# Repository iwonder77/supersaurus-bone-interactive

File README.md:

# Supersaurus Bone Interactive

Three-channel 555 monostable timer board driving RGB LED strips for a guess-the-dinosaur-bone exhibit at Thanksgiving Point's Museum of Ancient Life.

https://github.com/user-attachments/assets/5193e17a-1725-41bf-98e3-4b2cfe211b8b

---

## At a Glance

|                        |                                                               |
| ---------------------- | ------------------------------------------------------------- |
| **Supply**             | 12 V DC, single rail                                          |
| **Channels**           | 3 (one per answer slot)                                       |
| **Input per channel**  | Littlefuse reed switch (slot occupancy) AND master pushbutton |
| **Output pulse width** | `~3.63s` - set by R`33k` / C`100uF`                           |
| **Load per channel**   | 12V RGB LED strip, 1.67 A measured                            |
| **Load switching**     | Off-board N-channel MOSFET module, low-side                   |
| **PCB**                | `2-layer, 1 oz copper, HASL, 1.6 mm`                          |
| **Assembly**           | `JLCPCB Assembly and hand soldered`                           |
| **Active logic**       | Trigger is active-LOW; LED output is active-HIGH              |

---

## Overview

The Supersaurus bone interactive at Thanksgiving Point's Museum of Ancient Life invites visitors to guess which dinosaur the Supersaurus is related to based solely on scapula bone graphics. Guests place the Supersaurus scapula into one of three slots, each corresponding to a different dinosaur with its own scapula graphic. When they're ready to check their answer, they press a button, and an LED light strip installed behind the frosted acrylic slots briefly lights up red or green, providing immediate feedback on their guess.

When presented with the requirements of this project, my mind immediately jumped to using basic GPIO pins on a microcontroller to read the inputs, debounce them in software, and trigger a switching module for the lights. Even though that may have worked, removing software entirely for a three-input interaction with fixed timing removes an entire set of failure modes. A discrete analog implementation has no boot time, no watchdog to tune, and no flash to corrupt on abrupt power loss.

## Hardware Design Requirements

The interactive needed a circuit that:

- Debounces reed switch + button inputs for a smooth user experience
- Triggers immediate feedback on their answer for a short duration
- Resets the system quickly to not spoil the answer for the next guest
- Draws minimal power to handle reliable long term operation (next to 0 maintenance on parts)

These requirements quickly led to using a 555 timer in monostable mode to handle the timing portion of the interactive, and a MOSFET circuit to handle the fast and power efficient switching of a higher current load (LED strips).

## Main Hardware Components

- T.I. NE555P Timer ([datasheet](https://www.ti.com/lit/ds/symlink/ne555.pdf?ts=1777883502652))
- IRF520 MOSFET ([datasheet](https://www.vishay.com/docs/91017/irf520.pdf))
- PWM RGB LED Strips [link](https://www.amazon.com/dp/B0FSWXXXD4?ref=fed_asin_title&th=1)

The full BOM is included in the `manufacturing/` folder

## Full Schematic

## Main Hardware Architecture

Each 555 timer's TRIG pin is connected to a single reed switch (mounted behind the slot guests put the bone in), and each reed switch feeds into one "master" N.O. button. RC/pull up networks are configured for each TRIG pin to ensure smooth and predictable switching. This configuration allows the TRIG pin on each 555 timer to be pulled LOW only when its corresponding reed switch is closed **and** the button is pressed.

The three 555 timers are used in monostable mode to output a short pulse signal on pin Q when the TRIG pin is pulled low. More on monostable mode and the duration of the pulse below. The output signal (~10.3V when VCC = 12V) is fed into the gate of a IRF520 N-channel MOSFET module, which switches the low side of an RGB LED Strip for as long as the gate is driven.

## 555 Timer Notes

### Monostable Mode

Shorting the DISCHARGE and THRESHOLD pins of the 555 timer and routing them to an RC circuit operates the 555 timer in monostable mode. Ben Eater has a really great and informative series on the different 555 timer modes, I highly recommend watching them. Here's the one about [monostable mode](https://www.youtube.com/watch?v=81BgFhm2vz8).

In any case, the formula for the output signal duration is

$$
t_w = 1.1 \times R_A \times C
$$

Where $R_A$ and $C$ are the values of the resistor and capacitor. For future boards I wanted to make this duration configurable by having three open jumpers routed to resistors of different values (22k, 33k, 47k). The output pulse duration would change depending on which jumper is soldered.

Note: the trigger pulse must be shorter than $t_w$ and below $\frac{1}{3}V_{CC}$ (the 555's internal comparator threshold). If TRIG remains below $\frac{1}{3}V_{CC}$ beyond $t_w$, the output holds HIGH until TRIG rises.

### Power-on Reset Circuit

The 0.22uF and 10k RC network on the 555's RESET pin form a POR (power-on reset) circuit. During initial power-up testing without it, the output (Q) pin produced occasional HIGH pulses due to undefined internal states of the IC, which turned on downstream LED strips. This RC network briefly holds RESET low during power-up, forcing Q in a known LOW state while internal circuitry stabilizes. As the 0.22uF capacitor charges, RESET rises to VCC and normal operation begins, preventing false triggering at startup.

### Output (Q) Voltage

When triggered, the output voltage on pin Q isn't necessarily equal to VCC. When powered by 5V, I measured outputs of ~3.3V. When powered by 12V, I measured outputs of ~10.3V. The datasheet confirms this slight drop in voltage, and it is important to know since we'll be using it to drive the gate of an N-Channel MOSFET.

## MOSFET Selection and Gate Drive Design Notes

### Role

The main design requirements that guided my MOSFET selection were the following

- Fast switch times of 12V RGB LED strip loads (on the order of 1-2A)
- Minimal power dissipation
- Predictable operating behavior

Although quite outdated, the IRF520 N-Channel MOSFET was initially selected due to its accessibility, very low cost, and basic matching of electrical characteristics to the requirements described above (more on these below).

### Initial Implementation and Failure Mode

My initial prototype powered the 555 timer at VCC = 5V and used the output (Q) pin to directly drive the gate of an IRF520 MOSFET module. While the timing circuit functioned correctly, the LED strip failed to illuminate properly. This failure mode was not due to wiring or logic errors, but rather improper gate drive conditions for the selected MOSFET.

I'll start off by describing the important electrical characteristics we should know about for this design (for a deeper dive, refer to the [datasheet](https://www.vishay.com/docs/91017/irf520.pdf)). Then I'll discuss the proper gate drive design.

### Key Electrical Considerations

#### 1. $V_{GS(th)}$ Gate-Source Threshold Voltage

$V_{GS(th)} = 2.0\,\text{V}$ to $4.0\,\text{V}$ at $I_D = 250\,\mu\text{A}$

This parameter defines the voltage at which the MOSFET just barely begins to conduct a very small current - it is **not** an operating point for driving the gate and turning on the MOSFET. The best design drives the gate well past this threshold simply due to the fact that at higher gate voltages, the resistance between the drain-source ($R_{DS(on)}$) is much lower, leading to more efficient power operation.

#### 2. $R_{DS(on)}$ Drain-Source "on" Resistance

$R_{DS(on)} = 0.27\,\Omega$ at $V_{GS} = 10\,\text{V}$

For switching applications, the MOSFET must operate in the **ohmic (linear) region** (the $I_D$ vs. $V_{DS}$ graph below shows this region for various $V_{GS}$ curves) with as low a $R_{DS(on)}$ as possible. The lower the resistance, the less power is dissipated. To reach this lower resistance, we must drive the gate further and further from the threshold voltage (but don't exceed its maximum).

#### 3. $I_D$ vs. $V_{DS}$ graph at T = 25C (from datasheet)

<div align="center">
    <image src="docs/assets/ID-vs-VDS-curve.png" alt="id-vs-vds-curve">
</div>

In the ohmic region (linear region of the curves) the MOSFET acts like a voltage controlled resistor, where

$$
I_D = \frac{V_{DS}}{R_{DS(on)}}
$$

note that $R_{DS(on)}$ is not a fixed quantity, but decreases as $V_{GS}$ rises above $V_{GS(th)}$. The datasheet value of $0.27\,\Omega$ only holds at $V_{GS} = 10V$. Near the threshold voltage, it can be orders of magnitude higher, which directly increases power drawn ($P = I^2 * R$). Otherwise, in the saturation region, the MOSFET essentially acts as a current source, due to how the drain current $I_D$ stays nearly constant regardless of $V_{DS}$.

### Gate Drive Design

With the 555 timer powered at 5V, the output pin's HIGH voltage falls between 2.75V-3.3V (datasheet values). This is exactly in the MOSFET's $V_{GS(th)}$ range, where it barely starts to open and conduct current. Suppose our timer drove the gate at 3.3V, this would be a huge reliability concern, because:

- If the specific MOSFET we used had a $V_{GS(th)}$ = 2V: the MOSFET would slightly conduct
- If the MOSFET had a $V_{GS(th)}$ = 3.3V: the MOSFET would be right at threshold — essentially off
- If the MOSFET had a $V_{GS(th)}$ = 4V: the MOSFET wouldn't conduct at all

This doesn't even consider the inefficient power operation of the MOSFET in these conditions due to the very high $R_{DS(on)}$ and the 12V LED strip load demand. To ensure proper MOSFET operation, the gate drive voltage must be increased to a level where $R_{DS(on)}$ is low and well-defined.

Two viable approaches were considered:

#### Option 1: Use a Logic-Level MOSFET (IRLZ44N) with 5V supply for 555 timers

- Pros: compatible with lower level logic
- Cons: complicates power architecture (12V for LED strips and 5V for 555 timers)

#### Option 2: Increase Gate Drive Voltage (Selected)

Power the 555 timers at 12V (note: 5V sits at the lower bound of the NE555's recommended operating range, we should have started prototyping here). This results in:

- A gate drive voltage of ~10.3V
- A fully enhanced ("on") IRF520 with much lower $R_{DS(on)}$ and more manageable power dissipation
- A single 12V supply for the entire system

### Final Operating Behavior Calculations

Each LED strip draws 1.67A at 12V, measured directly on the bench. With the 555 timers powered at VCC = 12V, the gate sees ~10.3V - close to the datasheet condition of $V_{GS} = 10\text{V}$, so $R_{DS(on)} = 0.27\Omega$ applies directly.

The voltage drop across the MOSFET when fully on is

$$
V_{DS} = I_D \times R_{DS(on)} = 1.67\text{A} \times 0.27\Omega \approx 0.45\text{V}
$$

This confirms the MOSFET is in the ohmic region: ohmic operation requires $V_{DS} < V_{GS} - V_{GS(th)}$, and $0.45\text{V} \ll 10\text{V} - 2\text{V} = 8\text{V}$. The power dissipated by the MOSFET is then:

$$
P = I_D^2 \times R_{DS(on)} = (1.67\text{A})^2 \times 0.27\Omega \approx 0.75\text{W}
$$

At 0.75W, the IRF520 in its TO-220 package dissipates comfortably without a heatsink - a viable operating point for this application.

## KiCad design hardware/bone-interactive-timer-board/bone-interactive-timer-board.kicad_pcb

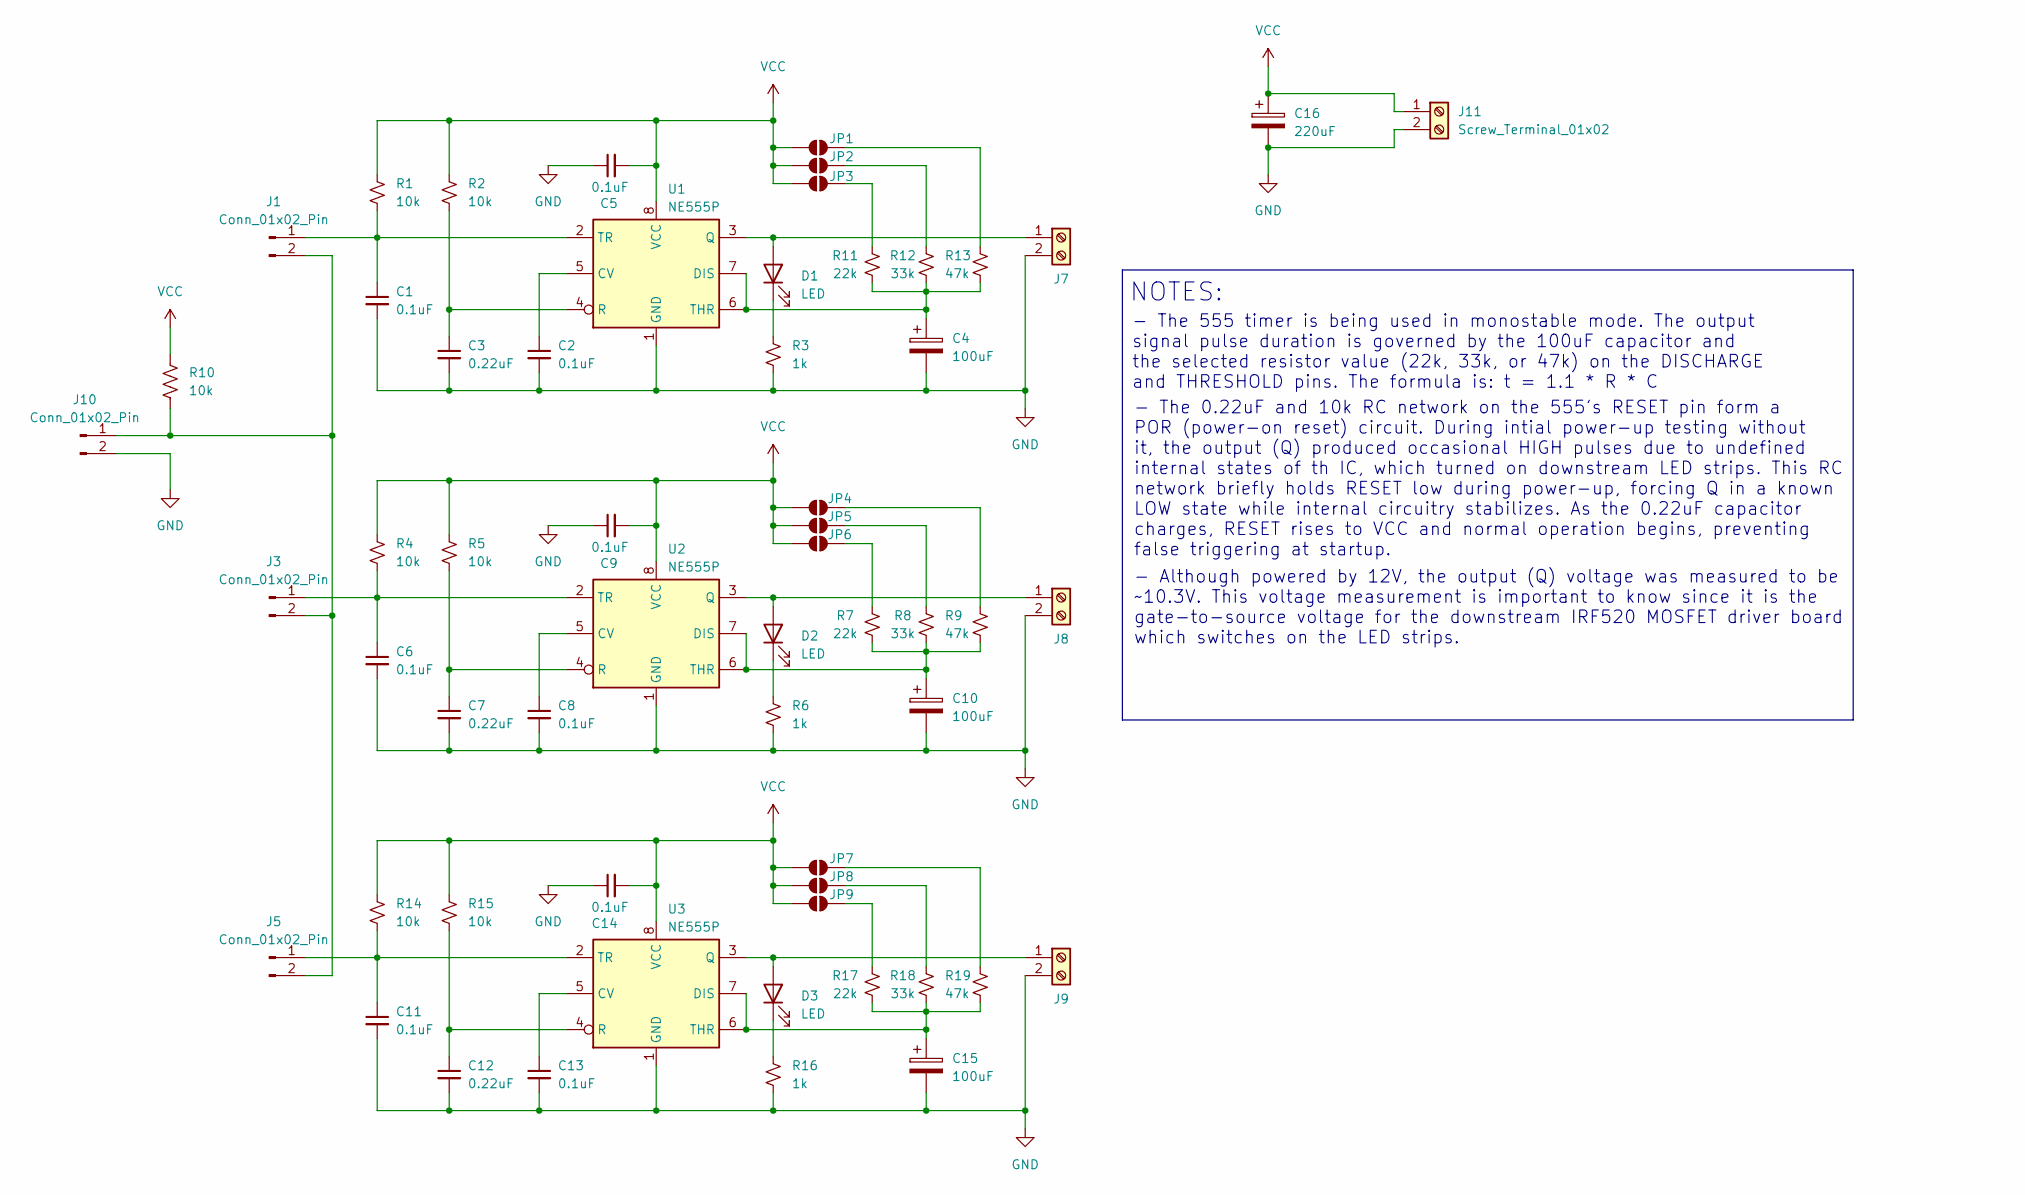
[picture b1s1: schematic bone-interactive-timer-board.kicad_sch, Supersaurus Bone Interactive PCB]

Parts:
C1, C2, C5, C6, C8, C9, C11, C13, C14: 0.1uF; C_0603_1608Metric
C3, C7, C12: 0.22uF; C_0603_1608Metric
C4, C10, C15: 100uF; CP_Elec_6.3x5.4
C16: 220uF; CP_Radial_D7.5mm_P2.50mm
D1, D2, D3: LED; LED_1206_3216Metric
J1, J3, J5, J10: Conn_01x02_Pin; PinHeader_1x02_P2.54mm_Vertical
J7, J8, J9, J11: Screw_Terminal_01x02; TerminalBlock_Phoenix_MPT-0,5-2-2.54_1x02_P2.54mm_Horizontal
JP1, JP2, JP3, JP4, JP5, JP6, JP7, JP8, JP9: SolderJumper_2_Open; SolderJumper-2_P1.3mm_Open_RoundedPad1.0x1.5mm
R1, R2, R4, R5, R10, R14, R15: 10k; R_0603_1608Metric
R3, R6, R16: 1k; R_0805_2012Metric
R7, R11, R17: 22k; R_0603_1608Metric
R8, R12, R18: 33k; R_0603_1608Metric
R9, R13, R19: 47k; R_0603_1608Metric
U1, U2, U3: NE555P; DIP-8_W7.62mm

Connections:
GND: C1.2, C2.2, C3.2, C4.2, C5.1, C6.2, C7.2, C8.2, C9.1, C10.2, C11.2, C12.2, C13.2, C14.1, C15.2, C16.2, J7.2, J8.2, J9.2, J10.2, J11.2, R3.1, R6.1, R16.1, U1.1 (GND), U2.1 (GND), U3.1 (GND)
unnamed: D1.2 (A), J7.1, U1.3 (Q)
unnamed: D1.1 (K), R3.2
unnamed: D2.2 (A), J8.1, U2.3 (Q)
unnamed: D2.1 (K), R6.2
unnamed: D3.2 (A), J9.1, U3.3 (Q)
unnamed: D3.1 (K), R16.2
unnamed: C1.1, J1.1, R1.2, U1.2 (TR)
unnamed: J1.2, J3.2, J5.2, J10.1, R10.2
unnamed: C6.1, J3.1, R4.2, U2.2 (TR)
unnamed: C11.1, J5.1, R14.2, U3.2 (TR)
unnamed: JP1.2 (B), R13.2
unnamed: JP2.2 (B), R12.1
unnamed: JP3.2 (B), R11.2
unnamed: JP4.2 (B), R9.2
unnamed: JP5.2 (B), R8.1
unnamed: JP6.2 (B), R7.2
unnamed: JP7.2 (B), R19.2
unnamed: JP8.2 (B), R18.1
unnamed: JP9.2 (B), R17.2
unnamed: C2.1, U1.5 (CV)
unnamed: C4.1, R11.1, R12.2, R13.1, U1.6 (THR), U1.7 (DIS)
unnamed: C3.1, R2.2, U1.4 (R)
unnamed: C8.1, U2.5 (CV)
unnamed: C10.1, R7.1, R8.2, R9.1, U2.6 (THR), U2.7 (DIS)
unnamed: C7.1, R5.2, U2.4 (R)
unnamed: C13.1, U3.5 (CV)
unnamed: C15.1, R17.1, R18.2, R19.1, U3.6 (THR), U3.7 (DIS)
unnamed: C12.1, R15.2, U3.4 (R)
VCC: C5.2, C9.2, C14.2, C16.1, J11.1, JP1.1 (A), JP2.1 (A), JP3.1 (A), JP4.1 (A), JP5.1 (A), JP6.1 (A), JP7.1 (A), JP8.1 (A), JP9.1 (A), R1.1, R2.1, R4.1, R5.1, R10.1, R14.1, R15.1, U1.8 (VCC), U2.8 (VCC), U3.8 (VCC)

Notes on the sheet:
- Although powered by 12V, the output (Q) voltage was measured to be ~10.3V. This voltage measurement is important to know since it is the gate-to-source voltage for the downstream IRF520 MOSFET driver board which switches on the LED strips.
NOTES:
- The 555 timer is being used in monostable mode. The output signal pulse duration is governed by the 100uF capacitor and the selected resistor value (22k, 33k, or 47k) on the DISCHARGE and THRESHOLD pins. The formula is: t = 1.1 * R * C
- The 0.22uF and 10k RC network on the 555's RESET pin form a POR (power-on reset) circuit. During intial power-up testing without it, the output (Q) produced occasional HIGH pulses due to undefined internal states of th IC, which turned on downstream LED strips. This RC network briefly holds RESET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

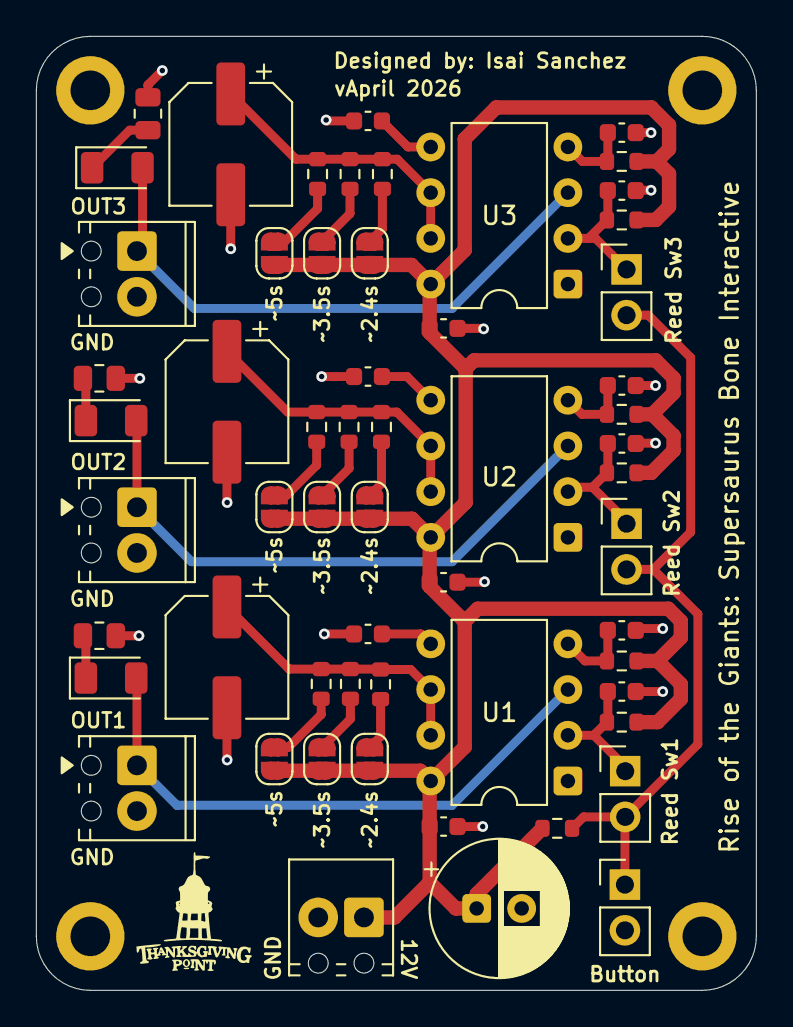
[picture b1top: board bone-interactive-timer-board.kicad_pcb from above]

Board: 2 copper layers, 40.0 x 53.0 mm, 58 parts (0 on the bottom side), 30 nets.

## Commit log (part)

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2026-05-04 title fix
2026-05-04 Update README.md with video
2026-05-04 overview paragraph written
2026-05-04 overview paragraph restructured
2026-05-04 overview paragraph rewritten
2026-05-04 first docs/ commit
2026-05-04 added main hardware list and full schematic
2026-05-04 fix path to full schematic file
2026-05-04 fix path to image
2026-05-04 renaming files
2026-05-04 fixing path to file
2026-05-04 add Hardware Architecture summary
2026-05-05 add relevant notes about 555 timer
2026-05-05 add initial IRF520 N-channel MOSFET notes
2026-05-05 fixing latex
2026-05-05 add important electrical characteristics
2026-05-05 add id vs vds curve png
2026-05-05 fix latex
2026-05-05 centering image
2026-05-05 fix indentation
2026-05-05 add explanation why we can't drive the gate with near logic-level voltages
2026-05-05 fix structure of MOSFET notes
2026-05-05 clean up section where explanation on why MOSFET being driven by 3.3v at the gate is not ideal at all
2026-05-05 add final edits before revamped MOSFET selection section
2026-05-05 restructure mosfet section
2026-05-05 clean formatting
2026-05-07 include design requirements in README
2026-05-07 cleaning up MOSFET section
2026-05-07 remove commas
